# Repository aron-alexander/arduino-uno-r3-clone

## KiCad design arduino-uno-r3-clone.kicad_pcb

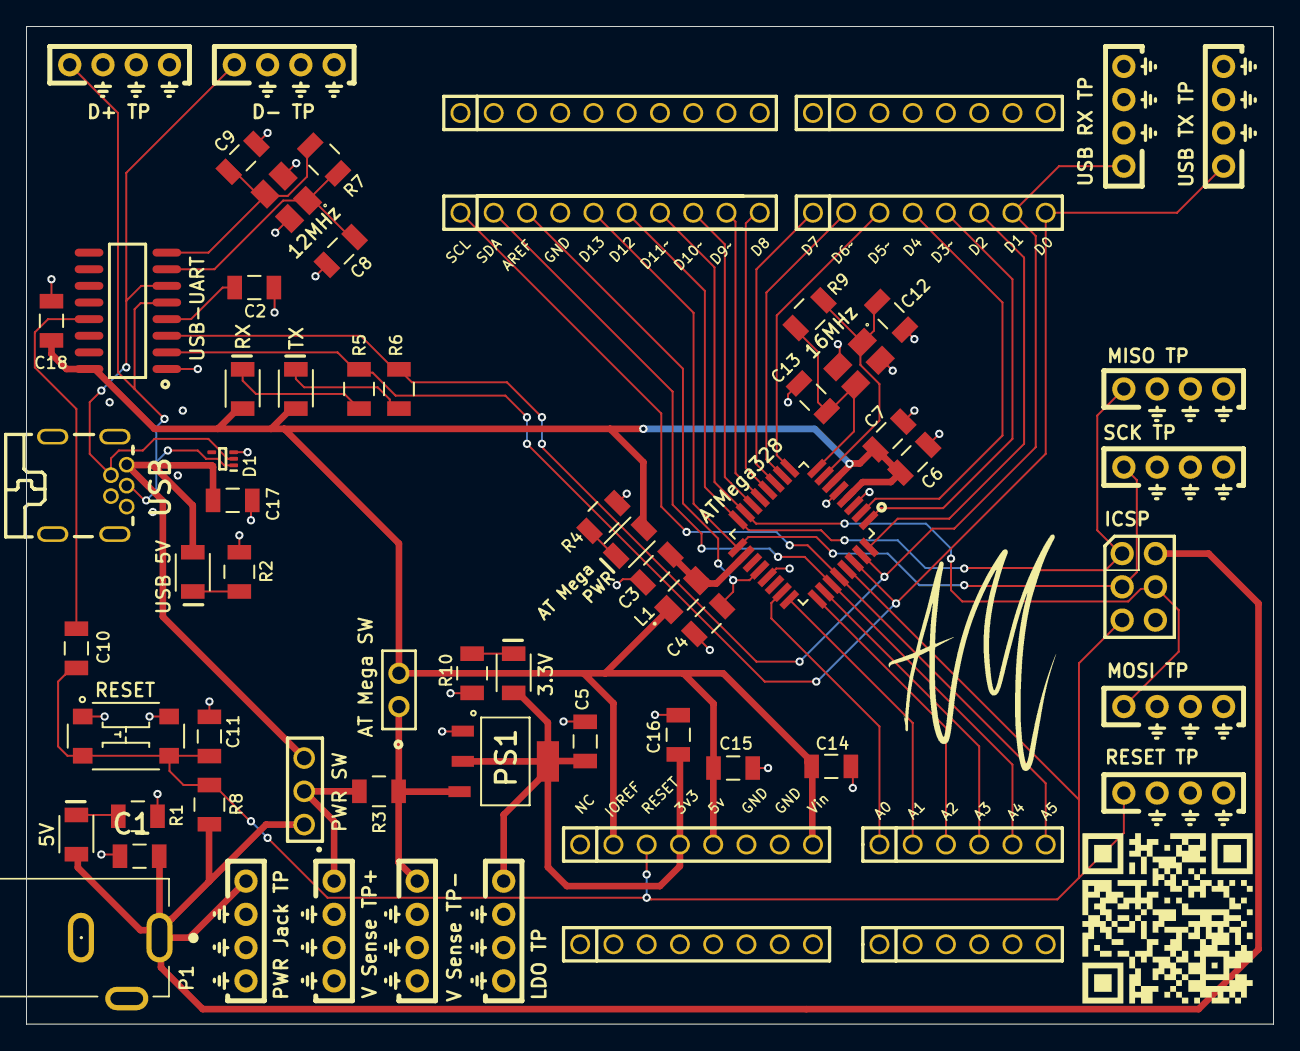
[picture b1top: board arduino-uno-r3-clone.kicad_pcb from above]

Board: 2 copper layers, 95.3 x 76.2 mm, 67 parts (0 on the bottom side), 44 nets.

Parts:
3.3V, 5V: Red; LED_1206
12MHz: X322512MSB4SI; Crystal resonator
16MHz: X322516MLB4SI; Crystal resonator
AT Mega : Green; LED_1206
AT Mega SW: SW_2Pin_100mil_Switch; 2Pin-Header-Conn
ATMega328: ATMEGA328P-ANR; ATMega328P
C1, C2, C3, C4, C5, C6, C7, C14, C15, C16, C17, C18: 22uF; 1206_Passive_Capacitor
C8, C9, C12, C13: 22pF; 1206_Passive_Capacitor
C10: 1uF; 1206_Passive_Capacitor
C11: 47nF; 1206_Passive_Capacitor
D1: Comment; SOTFL50P160X60-5N
D+ TP: 10x Probe TP; TP10x_Probe
D- TP: 10x Probe TP; TP10x_Probe
ICSP: NRPN032PAEN-RC; ICSP
J3, J7: PPTC081LFBN-RC; 8_PIN_100MIL - Female
J4: PPTC081LFBN-RC; 8_PIN_ARD-DIG_100MIL
J5: PPTC101LFBN-RC; 10_PIN_ARDUINO_100MIL
J6: PPTC101LFBN-RC; 10_PIN_100MIL - Female
J8: PPTC081LFBN-RC; 8_PIN_ARD-PWR_100MIL
J9: PPTC061LFBN-RC; 6_PIN_ARD-Analog_100mil
J10: PPTC061LFBN-RC; 6_PIN_100MIL -Female
L1: FB_10uH_1206; AIML-1206_ABR-M
LDO TP: 10x Probe TP; TP10x_Probe
MISO TP: 10x Probe TP; TP10x_Probe
MOSI TP: 10x Probe TP; TP10x_Probe
P1: Power Jack; Power_Jack
PS1: AMS1117-3.3; LDO
PWR Jack TP: 10x Probe TP; TP10x_Probe
PWR SW: PREC003SAAN-RC; 3_PIN_100mil
R1, R2, R10: 1k; 1206_Passive_Resitor
R3: 1 Ohm; 1206_Passive_Resitor
R4, R6: 510Ohm; 1206_Passive_Resitor
R5: 300 Ohm; 1206_Passive_Resitor
R7, R9: 1M; 1206_Passive_Resitor
R8: 10k; 1206_Passive_Resitor
RESET: TL3305AF160QG; Switch_JLC
RESET TP: 10x Probe TP; TP10x_Probe
RX: Blue; LED_1206
SCK TP: 10x Probe TP; TP10x_Probe
TX: Yellow; LED_1206
USB: USB Mini; USB_MINI_B
USB 5V: Red; LED_1206
USB RX TP: 10x Probe TP; TP10x_Probe
USB TX TP: 10x Probe TP; TP10x_Probe
USB-UART: CH340G; USB to serial
V Sense TP+: 10x Probe TP; TP10x_Probe
V Sense TP-: 10x Probe TP; TP10x_Probe

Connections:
3.3V: 3.3V.1, C5.1, C16.2, J8.4, LDO TP.1, PS1.2, PS1.4
12M Xtal1: 12MHz.1, C8.2, R7.1, USB-UART.7
12M Xtal2: 12MHz.3, C9.2, R7.2, USB-UART.8
16M Xtal1: 16MHz.1, ATMega328.7, C12.2, R9.1
16M Xtal2: 16MHz.3, ATMega328.8, C13.2, R9.2
+5: 5V.1, C1.1, ICSP.4, P1.1, PWR Jack TP.1, PWR SW.1, R8.1
A0: ATMega328.23, J9.1
A1: ATMega328.24, J9.2
A2: ATMega328.25, J9.3
A3: ATMega328.26, J9.4
AREF: ATMega328.20, C4.1, J5.3
D2: ATMega328.32, J4.6
D3: ATMega328.1, J4.5
D4: ATMega328.2, J4.4
D5: ATMega328.9, J4.3
D6: ATMega328.10, J4.2
D7: ATMega328.11, J4.1
D8: ATMega328.12, J5.10
D9: ATMega328.13, J5.9
D10: ATMega328.14, J5.8
D+: D1.1, D+ TP.1, USB.3, USB-UART.5
D-: D1.2, D- TP.1, USB.2, USB-UART.6
DTR: C10.2, USB-UART.13
GND: 12MHz.2, 12MHz.4, 16MHz.2, 16MHz.4, ATMega328.3, ATMega328.5, ATMega328.21, C1.2, C2.2, C3.2, C4.2, C5.2, C6.2, C7.2, C8.1, C9.1, C11.1, C12.1, C13.1, C14.1, C15.1, C16.1, C17.1, C18.2, D1.3, D+ TP.2, D- TP.2, ICSP.6, J3.1, J3.2, J3.3, J3.4, J3.5, J3.6, J3.7, J3.8, J5.4, J6.1, J6.2, J6.3, J6.4, J6.5, J6.6, J6.7, J6.8, J6.9, J6.10, J7.1, J7.2, J7.3, J7.4, J7.5, J7.6, J7.7, J7.8, J8.6, J8.7, J10.1, J10.2, J10.3, J10.4, J10.5, J10.6, LDO TP.2, MISO TP.2, MOSI TP.2, P1.2, P1.3, PS1.1, PWR Jack TP.2, R1.1, R2.1, R4.1, R10.1, RESET.1, RESET.2, RESET TP.2, SCK TP.2, USB.5, USB.6, USB.7, USB.8, USB.9, USB RX TP.2, USB TX TP.2, USB-UART.1, V Sense TP+.2, V Sense TP-.2
MISO: ATMega328.16, ICSP.1, J5.6, MISO TP.1
MOSI: ATMega328.15, ICSP.5, J5.7, MOSI TP.1
Net3.3V PWR_2: 3.3V.2, R10.2
Net5V_2: 5V.2, R1.2
NetAT Mega PWR_2: AT Mega.2, R4.2
NetAT Mega SW_1: AT Mega SW.1, PS1.3, R3.1, V Sense TP-.1
NetATMega328_18: ATMega328.18, C3.1, L1.2
NetC2_1: C2.1, USB-UART.4
NetLED4_2: R5.1, RX.2
NetLED5_2: R6.1, TX.2
NetR2_2: R2.2, USB 5V.2
RESET: ATMega328.29, C10.1, C11.2, ICSP.3, J8.3, R8.2, RESET.3, RESET.4, RESET TP.1
SCK: ATMega328.17, ICSP.2, J5.5, SCK TP.1
SCL: ATMega328.28, J5.1, J9.6
SDA: ATMega328.27, J5.2, J9.5
USB 5V: C17.2, D1.5, PWR SW.3, USB.1, USB 5V.1
USB_RX: ATMega328.31, J4.7, R6.2, USB RX TP.1, USB-UART.3
USB_TX: ATMega328.30, J4.8, R5.2, USB TX TP.1, USB-UART.2
V Sense: PWR SW.2, R3.2, V Sense TP+.1
VCC: AT Mega.1, AT Mega SW.2, ATMega328.4, ATMega328.6, C6.1, C7.1, C14.2, C15.2, C18.1, J8.2, J8.5, J8.8, L1.1, RX.1, TX.1, USB-UART.16
